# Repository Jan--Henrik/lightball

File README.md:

# lightball

Don't build this, it does not work

Replacement PCB for cheap flying "lightballs" from china, adds device control, controllable LEDs and wifi.

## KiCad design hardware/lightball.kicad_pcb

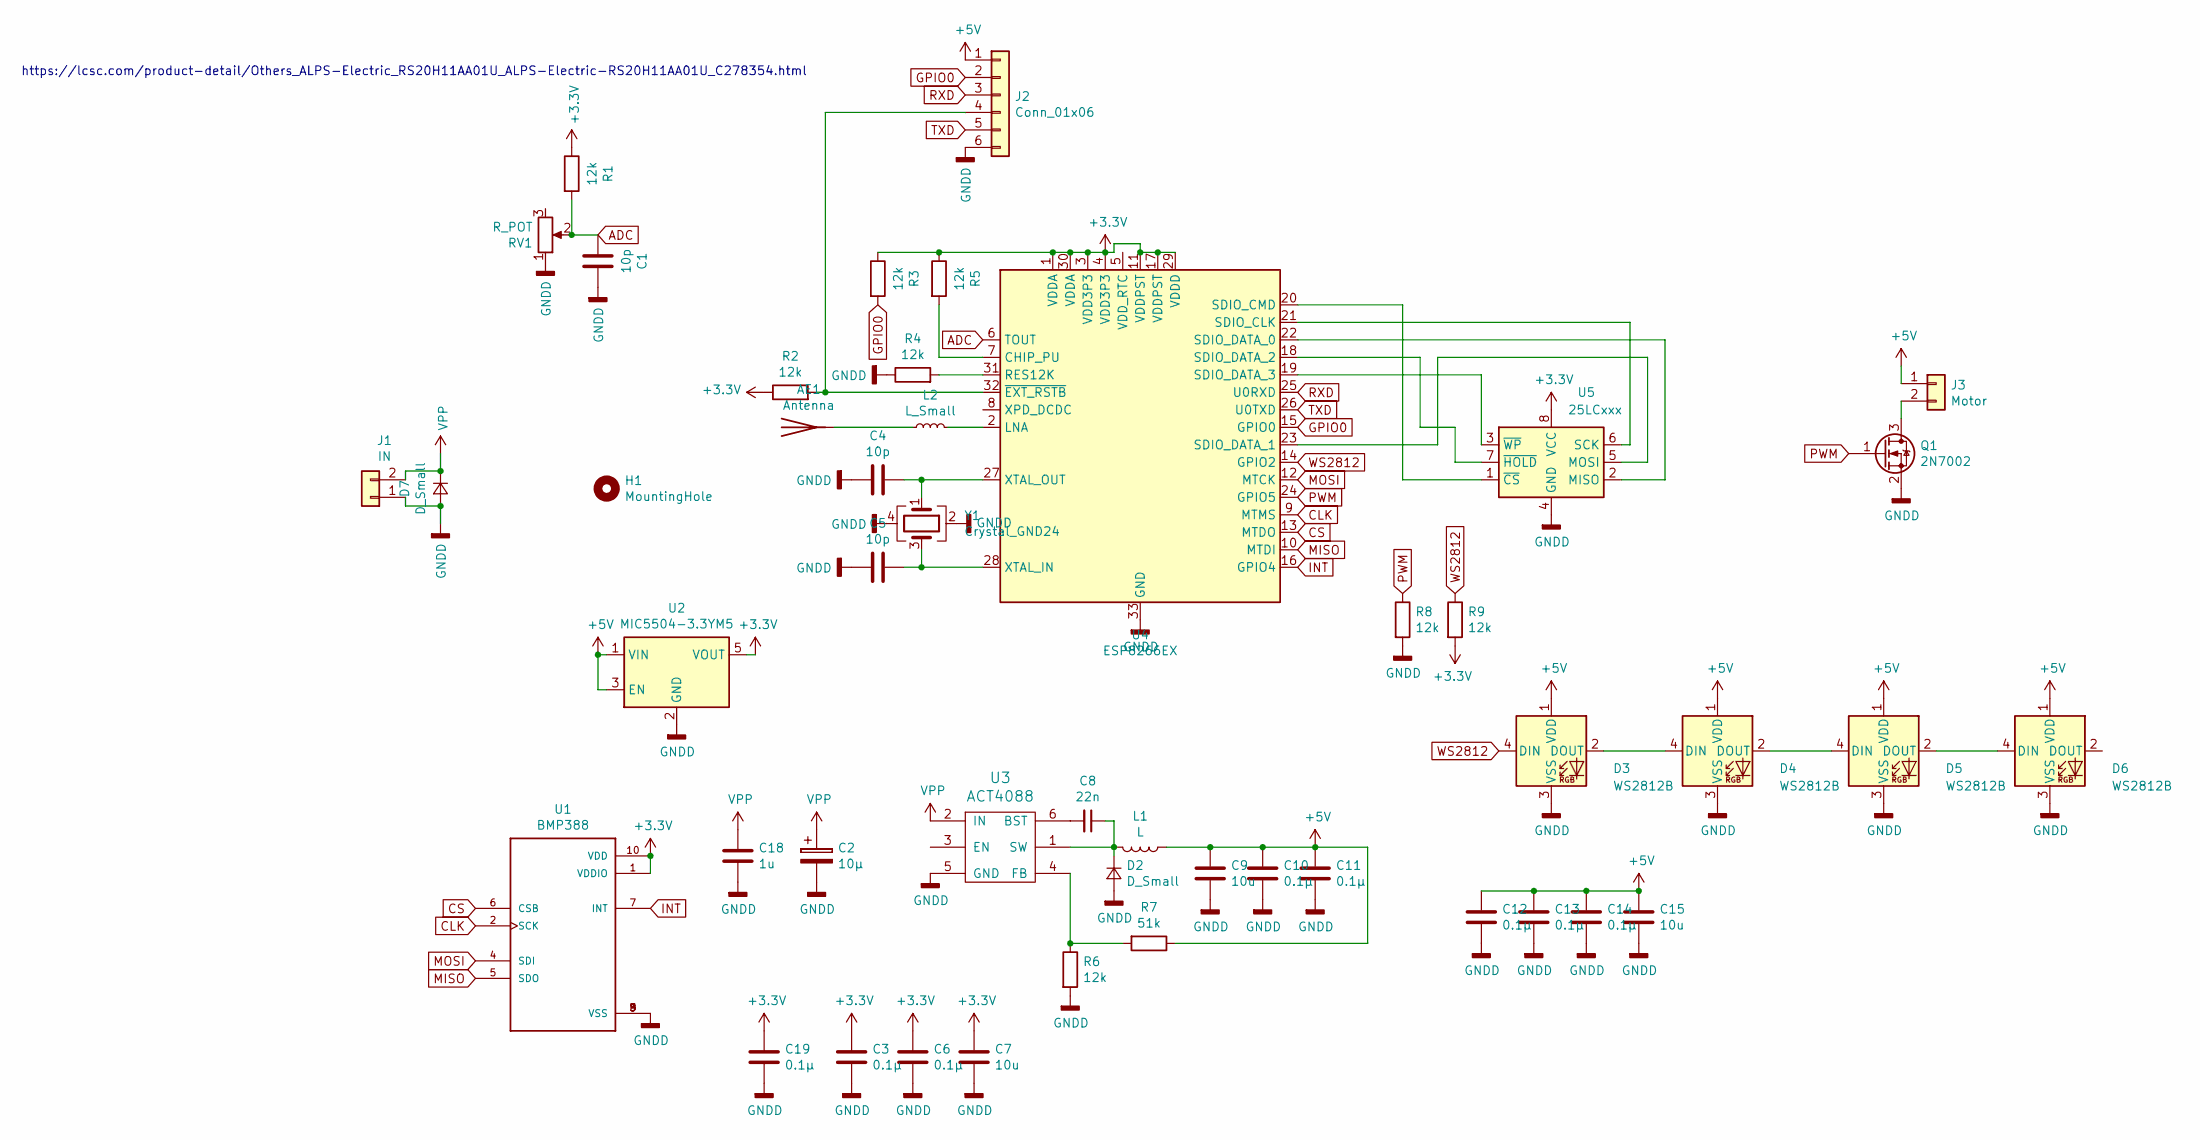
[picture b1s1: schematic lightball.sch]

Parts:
AE1: Antenna; TestPoint_Pad_1.0x1.0mm
C1: 10p; C_0402_1005Metric
C2: 10µ; CP_Radial_D5.0mm_P2.50mm
C3, C10, C11: 0.1µ; C_0603_1608Metric
C4, C5: 10p; C_0603_1608Metric
C6, C12, C13, C14, C19: 0.1µ; C_0402_1005Metric
C7, C9: 10u; C_0603_1608Metric
C8: 22n; C_0402_1005Metric
C15: 10u; C_0402_1005Metric
C18: 1u; C_0603_1608Metric
D2, D7: D_Small; D_SOD-123
D3, D4, D5, D6: WS2812B; LED_WS2812B_PLCC4_5.0x5.0mm_P3.2mm
H1: MountingHole; PinHeader_1x01_P2.54mm_Vertical
J1: IN; PinHeader_1x02_P2.54mm_Vertical
J2: Conn_01x06; PinSocket_1x06_P1.27mm_Vertical
J3: Motor; PinHeader_1x02_P2.54mm_Vertical
L1: L; SMD_INDUCTOR_32x25
L2: L_Small; L_0603_1608Metric
Q1: 2N7002; SOT-23
R1, R2, R3, R4, R5, R6, R8, R9: 12k; R_0402_1005Metric
R7: 51k; R_0402_1005Metric
RV1: R_POT; RS20H11AA015
U1: BMP388; PQFN50P200X200X80-10N
U2: MIC5504-3.3YM5; SOT-23-5
U3: ACT4088; SOT-23-6
U4: ESP8266EX; QFN-32-1EP_5x5mm_P0.5mm_EP3.45x3.45mm
U5: 25LCxxx; SOIJ-8_5.3x5.3mm_P1.27mm
Y1: Crystal_GND24; Crystal_SMD_SeikoEpson_FA238-4Pin_3.2x2.5mm

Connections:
+3V3: C3.1, C6.1, C7.1, C19.1, R1.1, R2.1, R3.1, R5.1, R9.2, U1.1 (VDDIO), U1.10 (VDD), U2.5 (VOUT), U4.1 (VDDA), U4.3 (VDD3P3), U4.4 (VDD3P3), U4.11 (VDDPST), U4.17 (VDDPST), U4.29 (VDDD), U4.30 (VDDA), U5.8 (VCC)
+5V: C9.1, C10.1, C11.1, C12.1, C13.1, C14.1, C15.1, D3.1 (VDD), D4.1 (VDD), D5.1 (VDD), D6.1 (VDD), J2.1, J3.1, L1.1, R7.1, U2.1 (VIN), U2.3 (EN)
ADC: C1.2, R1.2, RV1.2, U4.6 (TOUT)
CLK: U1.2 (SCK), U4.9 (MTMS)
CS: U1.6 (CSB), U4.13 (MTDO)
GNDD: C1.1, C2.2, C3.2, C4.2, C5.2, C6.2, C7.2, C9.2, C10.2, C11.2, C12.2, C13.2, C14.2, C15.2, C18.2, C19.2, D2.2 (A), D3.3 (VSS), D4.3 (VSS), D5.3 (VSS), D6.3 (VSS), D7.2 (A), J1.1, J2.6, Q1.2 (S), R4.1, R6.2, R8.2, RV1.1, U1.3 (VSS), U1.8 (VSS), U1.9 (VSS), U2.2 (GND), U3.5 (GND), U4.33 (GND), U5.4 (GND), Y1.2, Y1.4
GPIO0: J2.2, R3.2, U4.15 (GPIO0)
INT: U1.7 (INT), U4.16 (GPIO4)
MISO: U1.5 (SDO), U4.10 (MTDI)
MOSI: U1.4 (SDI), U4.12 (MTCK)
unnamed: AE1.1, L2.1
unnamed: C4.1, U4.27 (XTAL_OUT), Y1.1
unnamed: C5.1, U4.28 (XTAL_IN), Y1.3
unnamed: C8.1, D2.1 (K), L1.2, U3.1 (SW)
unnamed: C8.2, U3.6 (BST)
unnamed: D3.2 (DOUT), D4.4 (DIN)
unnamed: D4.2 (DOUT), D5.4 (DIN)
unnamed: D5.2 (DOUT), D6.4 (DIN)
unnamed: J2.4, R2.2, U4.32 (~EXT_RSTB~)
unnamed: J3.2, Q1.3 (D)
unnamed: L2.2, U4.2 (LNA)
unnamed: R4.2, U4.31 (RES12K)
unnamed: R5.2, U4.7 (CHIP_PU)
unnamed: R6.1, R7.2, U3.4 (FB)
unnamed: U4.18 (SDIO_DATA_2), U5.7 (~HOLD)
unnamed: U4.19 (SDIO_DATA_3), U5.3 (~WP)
unnamed: U4.20 (SDIO_CMD), U5.1 (~CS)
unnamed: U4.21 (SDIO_CLK), U5.6 (SCK)
unnamed: U4.22 (SDIO_DATA_0), U5.2 (MISO)
unnamed: U4.23 (SDIO_DATA_1), U5.5 (MOSI)
PWM: Q1.1 (G), R8.1, U4.24 (GPIO5)
RXD: J2.3, U4.25 (U0RXD)
TXD: J2.5, U4.26 (U0TXD)
VPP: C2.1, C18.1, D7.1 (K), J1.2, U3.2 (IN)
WS2812: D3.4 (DIN), R9.1, U4.14 (GPIO2)

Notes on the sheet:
https://lcsc.com/product-detail/Others_ALPS-Electric_RS20H11AA01U_ALPS-Electric-RS20H11AA01U_C278354.html

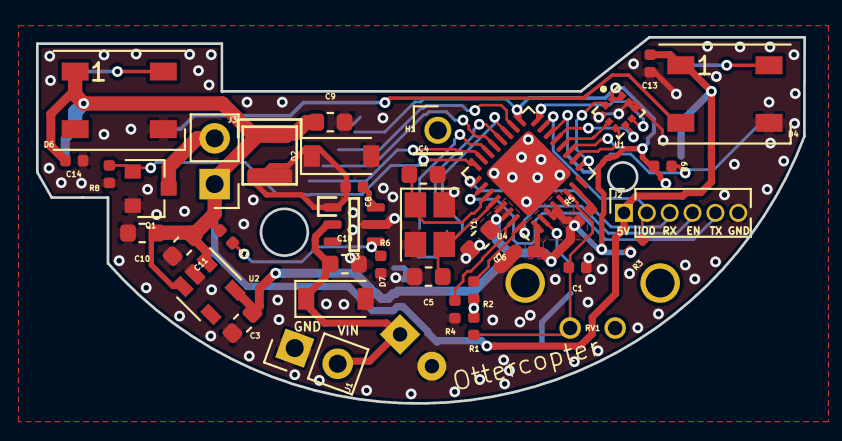
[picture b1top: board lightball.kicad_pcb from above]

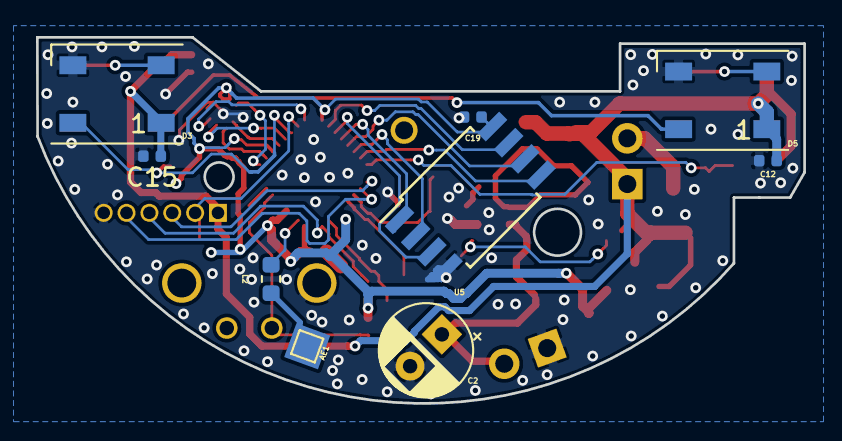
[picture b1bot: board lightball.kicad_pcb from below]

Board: 2 copper layers, 42.6 x 20.3 mm, 47 parts (9 on the bottom side), 35 nets.

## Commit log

2018-12-21 added firmware
2018-12-21 moved hardware
2018-12-21 updated gerber
